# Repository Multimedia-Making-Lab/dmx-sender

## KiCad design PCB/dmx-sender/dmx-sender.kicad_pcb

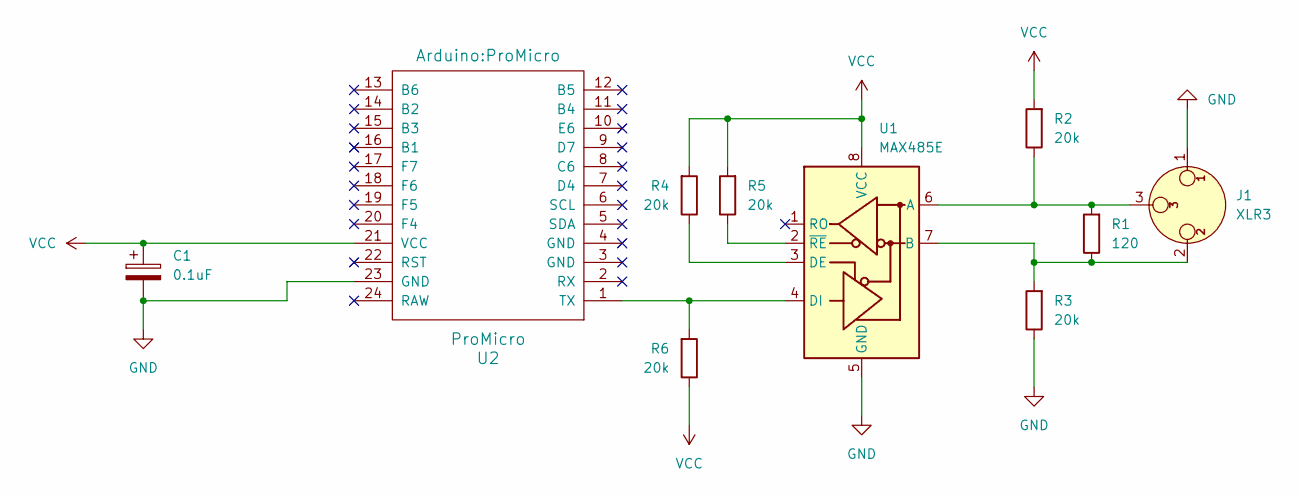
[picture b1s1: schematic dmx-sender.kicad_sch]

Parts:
C1: 0.1uF; CP_Radial_D5.0mm_P2.50mm
J1: XLR3; Jack_XLR_Neutrik_NC3MAAH-0_Horizontal
R1: 120; R_Axial_DIN0207_L6.3mm_D2.5mm_P7.62mm_Horizontal
R2, R3, R4, R5, R6: 20k; R_Axial_DIN0207_L6.3mm_D2.5mm_P7.62mm_Horizontal
U1: MAX485E; DIP-8_W7.62mm_LongPads
U2: ProMicro

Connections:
GND: C1.2, J1.1, R3.1, U1.5 (GND), U2.23 (GND)
unnamed: J1.3, R1.2, R2.1, U1.6 (A)
unnamed: J1.2, R1.1, R3.2, U1.7 (B)
unnamed: R4.1, U1.3 (DE)
unnamed: R6.2, U1.4 (DI), U2.1 (TX)
unnamed: R5.1, U1.2 (~RE)
VCC: C1.1, R2.2, R4.2, R5.2, R6.1, U1.8 (VCC), U2.21 (VCC)

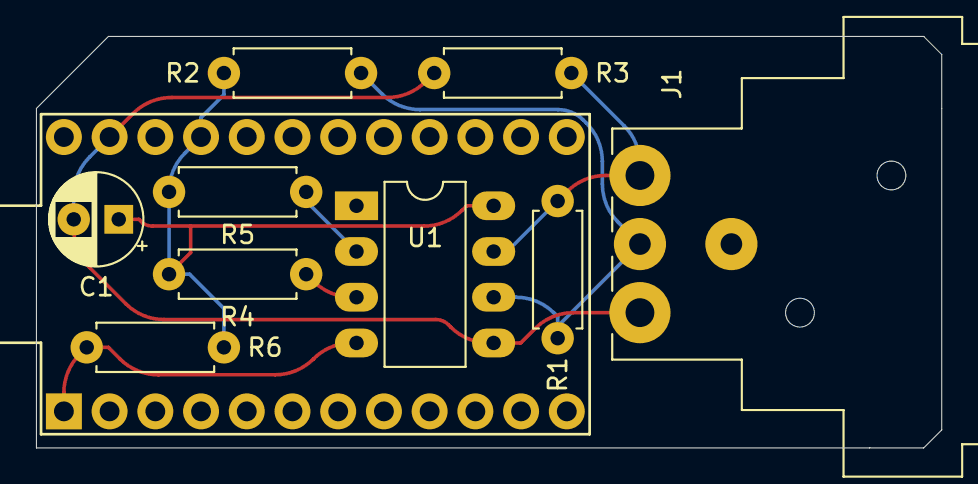
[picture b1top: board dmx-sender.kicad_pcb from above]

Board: 2 copper layers, 50.3 x 22.9 mm, 10 parts (0 on the bottom side), 7 nets.
